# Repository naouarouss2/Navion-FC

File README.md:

# Navion FC

## What is it
It is a small all-in-one flight controller used for autonomous vehicles.

It will run Ardupilot and is compatible with any type of autonomous vehicles.

## Features ✅
-  Barometer
-  IMU
-  Magnometer
-  10 PWM outputs
-  PPM/SBUS input
-  4 Neopixel outputs
-  MicroSD Card Reader
-  USB-C Connector
-  SWD Debugging Interface
-  3 UART Headers
-  1 USART Header
-  1 I²C Header
-  Safety Switch Header
-  16MB External Flash
-  Battery Voltage Monitoring
-  Up to 40V battery input voltage
## Why do I want to make it ? 🛠️

I have always been passionate about autonomous vehicles and wanted to build a universal solution that can run all of the vehicles I'll be building in the future.

That's why I made my flight controller extremely modular and versatile.

## How does it work ?

-  You attach all of your ESCs and Servos to the PWM outputs.

-  Attach neopixel strips to the top neopixel headers (You should power them externally).

-  Connect a standard Pixhawk 2.4.8 (or similar) GPS module (You need to swap the connectors for JST-XH connectors) to the GPS and I²C headers.

-  Connect the battery to the battery header.

-  Connect the RC receiver to the PPM/SBUS header (and configure it accordingly later).

-  Connect a telemetry module to the USART2 header.

-  You can connect other UART accessories like a Lidar to the UART2 and UART3 headers.

-  Then you configure your peripherals in **Mission Planner**, setup your flight controller, plan a mission, and you should be good to go !

## PCB 

### Schematic

### Routing

### 3D View

## 3D Deisgn 🎨

## Firmware

This flight controller will run a custom ported version of the **[Ardupilot firmware](https://github.com/ArduPilot/ardupilot)**

## Disclaimer ⚠️

This project is still untested.

## Credits ❤️
Project made by : **Oussama NAOUAR**

Total logged working hours : **40 hrs**

Made as part of the **Hack Club Fallout** program.

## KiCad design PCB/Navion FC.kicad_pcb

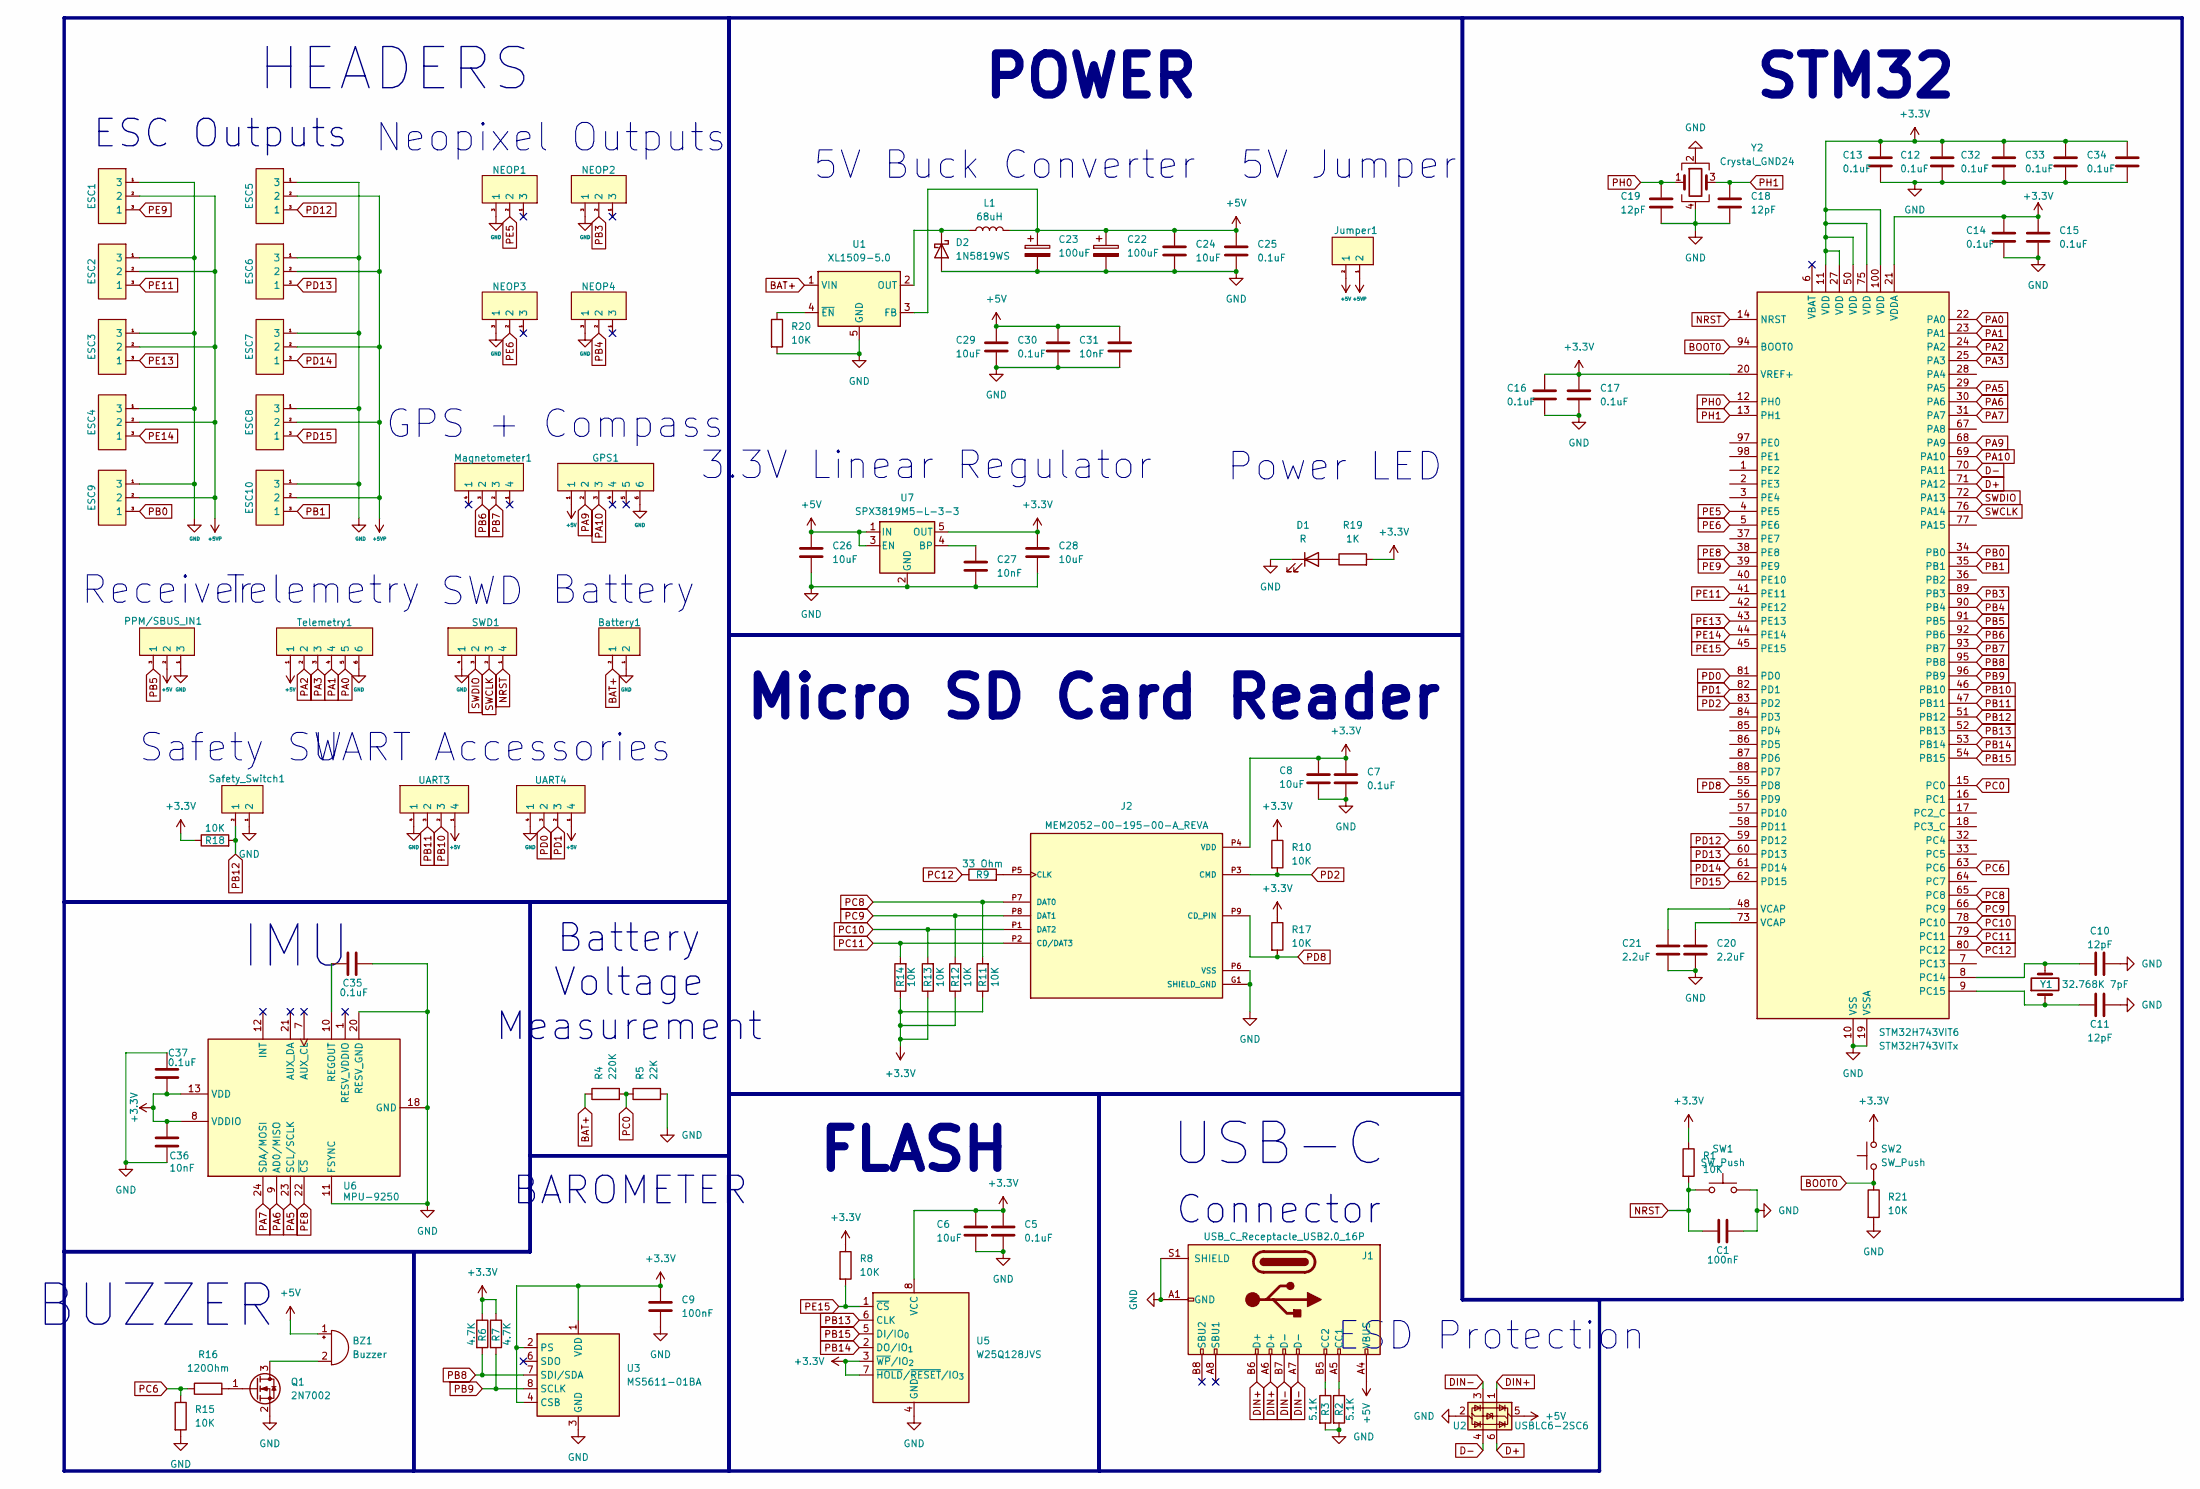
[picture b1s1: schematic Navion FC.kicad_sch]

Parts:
BZ1: Buzzer; Buzzer_12x9.5RM7.6
Battery1: JST_XH_B2B-XH-A_1x02_P2.50mm_Vertical
C1, C9: 100nF; C_0603_1608Metric
C5, C7, C12, C13, C14, C15, C16, C17, C25, C30, C32, C33, C34, C35, C37: 0.1uF; C_0603_1608Metric
C6, C8, C24, C26, C28, C29: 10uF; C_0603_1608Metric
C10, C11, C18, C19: 12pF; C_0603_1608Metric
C20, C21: 2.2uF; C_0603_1608Metric
C22, C23: 100uF; CP_EIA-3528-21_Kemet-B
C27, C31, C36: 10nF; C_0603_1608Metric
D1: R; LED_0603_1608Metric
D2: 1N5819WS; D_SOD-323
ESC1, ESC2, ESC3, ESC4, ESC5, ESC6, ESC7, ESC8, ESC9, ESC10: PinHeader_1x03_P2.54mm_Vertical
GPS1: JST_XH_B6B-XH-A_1x06_P2.50mm_Vertical
J1: USB_C_Receptacle_USB2.0_16P; USB_C_Receptacle_HCTL_HC-TYPE-C-16P-01A
J2: MEM2052-00-195-00-A_REVA; GCT_MEM2052-00-195-00-A_REVA; PARTREV A
Jumper1: PinHeader_1x02_P2.54mm_Vertical
L1: 68uH; L_Sunlord_SWPA8040S
Magnetometer1: JST_XH_B4B-XH-A_1x04_P2.50mm_Vertical
NEOP1, NEOP2, NEOP3, NEOP4: JST_XH_B3B-XH-A_1x03_P2.50mm_Vertical
PPM/SBUS_IN1: PinHeader_1x03_P2.54mm_Vertical
Q1: 2N7002; SOT-23
R1, R8, R10, R11, R12, R13, R14, R15, R17, R18, R20, R21: 10K; R_0603_1608Metric
R2, R3: 5.1K; R_0603_1608Metric
R4: 220K; R_0603_1608Metric
R5: 22K; R_0603_1608Metric
R6, R7: 4.7K; R_0603_1608Metric
R9: 33 Ohm; R_0603_1608Metric
R16: 120Ohm; R_0603_1608Metric
R19: 1K; R_0603_1608Metric
STM32H743VIT6: STM32H743VITx; LQFP-100_14x14mm_P0.5mm
SW1, SW2: SW_Push; SW_PUSH_6mm
SWD1: JST_XH_B4B-XH-A_1x04_P2.50mm_Vertical
Safety_Switch1: JST_XH_B2B-XH-A_1x02_P2.50mm_Vertical
Telemetry1: JST_XH_B6B-XH-A_1x06_P2.50mm_Vertical
U1: XL1509-5.0; SOIC-8_3.9x4.9mm_P1.27mm
U2: USBLC6-2SC6; SOT-23-6
U3: MS5611-01BA; LGA-8_3x5mm_P1.25mm
U5: W25Q128JVS; SOIC-8_5.3x5.3mm_P1.27mm
U6: MPU-9250; InvenSense_QFN-24_3x3mm_P0.4mm
U7: SPX3819M5-L-3-3; SOT-23-5
UART3, UART4: JST_XH_B4B-XH-A_1x04_P2.50mm_Vertical
Y1: 32.768K 7pF; Crystal_SMD_3215-2Pin_3.2x1.5mm
Y2: Crystal_GND24; Crystal_SMD_3225-4Pin_3.2x2.5mm

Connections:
+3.3V: C5.1, C6.1, C7.1, C8.1, C9.1, C12.1, C13.1, C14.1, C15.1, C16.1, C17.1, C28.1, C32.1, C33.1, C34.1, C36.2, C37.1, J2.P4 (VDD), R1.1, R6.1, R7.1, R8.1, R10.1, R11.1, R12.1, R13.1, R14.1, R17.1, R18.1, R19.2, STM32H743VIT6.11 (VDD), STM32H743VIT6.20 (VREF+), STM32H743VIT6.21 (VDDA), STM32H743VIT6.27 (VDD), STM32H743VIT6.50 (VDD), STM32H743VIT6.75 (VDD), STM32H743VIT6.100 (VDD), SW2.2, U3.1 (VDD), U3.2 (PS), U3.4 (CSB), U3.5 (CSB), U5.3 (~WP/IO_{2}), U5.7 (~HOLD/~RESET/IO_{3}), U5.8 (VCC), U6.8 (VDDIO), U6.13 (VDD), U7.5 (OUT)
+5V: BZ1.1 (+), C22.1, C23.1, C24.1, C25.1, C26.1, C29.1, C30.1, C31.1, GPS1.1, J1.A4 (VBUS), J1.A9 (VBUS), J1.B4 (VBUS), J1.B9 (VBUS), Jumper1.2 (1), L1.2, PPM/SBUS_IN1.2, Telemetry1.1, U1.3 (FB), U2.5 (VBUS), U7.1 (IN), U7.3 (EN), UART3.1 (4), UART4.1 (4)
+5VP: ESC1.2, ESC2.2, ESC3.2, ESC4.2, ESC5.2, ESC6.2, ESC7.2, ESC8.2, ESC9.2, ESC10.2, Jumper1.1 (2)
BAT+: Battery1.2 (1), R4.1, U1.1 (VIN)
BOOT0: R21.1, STM32H743VIT6.94 (BOOT0), SW2.1
D+: STM32H743VIT6.71 (PA12), U2.6 (I/O1)
D-: STM32H743VIT6.70 (PA11), U2.4 (I/O2)
DIN+: J1.A6 (D+), J1.B6 (D+), U2.1 (I/O1)
DIN-: J1.A7 (D-), J1.B7 (D-), U2.3 (I/O2)
GND: Battery1.1 (2), C1.2, C5.2, C6.2, C7.2, C8.2, C9.2, C10.2, C11.2, C12.2, C13.2, C14.2, C15.2, C16.2, C17.2, C18.2, C19.2, C20.2, C21.2, C22.2, C23.2, C24.2, C25.2, C26.2, C27.2, C28.2, C29.2, C30.2, C31.2, C32.2, C33.2, C34.2, C35.2, C36.1, C37.2, D1.1 (K), D2.2 (A), ESC1.1 (3), ESC2.1 (3), ESC3.1 (3), ESC4.1 (3), ESC5.1 (3), ESC6.1 (3), ESC7.1 (3), ESC8.1 (3), ESC9.1 (3), ESC10.1 (3), GPS1.6, J1.A1 (GND), J1.A12 (GND), J1.B1 (GND), J1.B12 (GND), J1.S1 (SHIELD), J2.G1 (SHIELD_GND), J2.G2 (SHIELD_GND), J2.G3 (SHIELD_GND), J2.G4 (SHIELD_GND), J2.P6 (VSS), NEOP1.3 (1), NEOP2.3 (1), NEOP3.3 (1), NEOP4.3 (1), PPM/SBUS_IN1.1 (3), Q1.2 (S), R2.2, R3.2, R5.2, R15.2, R20.2, R21.2, STM32H743VIT6.10 (VSS), STM32H743VIT6.19 (VSSA), STM32H743VIT6.26 (VSS), STM32H743VIT6.49 (VSS), STM32H743VIT6.74 (VSS), STM32H743VIT6.99 (VSS), SW1.2, SWD1.4 (1), Safety_Switch1.1 (2), Telemetry1.6, U1.5 (GND), U1.6 (GND), U1.7 (GND), U1.8 (GND), U2.2 (GND), U3.3 (GND), U5.4 (GND), U6.11 (FSYNC), U6.18 (GND), U6.20 (RESV_GND), U7.2 (GND), UART3.4 (1), UART4.4 (1), Y2.2, Y2.4
NRST: C1.1, R1.2, STM32H743VIT6.14 (NRST), SW1.1, SWD1.1 (4)
unnamed: BZ1.2 (-), Q1.3 (D)
unnamed: C20.1, STM32H743VIT6.73 (VCAP)
unnamed: C21.1, STM32H743VIT6.48 (VCAP)
unnamed: D1.2 (A), R19.1
unnamed: D2.1 (K), L1.1, U1.2 (OUT)
unnamed: J1.A5 (CC1), R2.1
unnamed: J1.B5 (CC2), R3.1
unnamed: J2.P5 (CLK), R9.2
unnamed: Q1.1 (G), R16.2
unnamed: C10.1, STM32H743VIT6.8 (PC14), Y1.2
unnamed: C11.1, STM32H743VIT6.9 (PC15), Y1.1
unnamed: R20.1, U1.4 (~EN)
unnamed: C35.1, U6.10 (REGOUT)
unnamed: C27.1, U7.4 (BP)
PA0: STM32H743VIT6.22 (PA0), Telemetry1.5
PA1: STM32H743VIT6.23 (PA1), Telemetry1.4
PA2: STM32H743VIT6.24 (PA2), Telemetry1.2
PA3: STM32H743VIT6.25 (PA3), Telemetry1.3
PA5: STM32H743VIT6.29 (PA5), U6.23 (SCL/SCLK)
PA6: STM32H743VIT6.30 (PA6), U6.9 (AD0/MISO)
PA7: STM32H743VIT6.31 (PA7), U6.24 (SDA/MOSI)
PA9: GPS1.2, STM32H743VIT6.68 (PA9)
PA10: GPS1.3, STM32H743VIT6.69 (PA10)
PB0: ESC9.3 (1), STM32H743VIT6.34 (PB0)
PB1: ESC10.3 (1), STM32H743VIT6.35 (PB1)
PB3: NEOP2.2, STM32H743VIT6.89 (PB3)
PB4: NEOP4.2, STM32H743VIT6.90 (PB4)
PB5: PPM/SBUS_IN1.3 (1), STM32H743VIT6.91 (PB5)
PB6: Magnetometer1.3 (2), STM32H743VIT6.92 (PB6)
PB7: Magnetometer1.2 (3), STM32H743VIT6.93 (PB7)
PB8: R6.2, STM32H743VIT6.95 (PB8), U3.7 (SDI/SDA)
PB9: R7.2, STM32H743VIT6.96 (PB9), U3.8 (SCLK)
PB10: STM32H743VIT6.46 (PB10), UART3.2 (3)
PB11: STM32H743VIT6.47 (PB11), UART3.3 (2)
PB12: R18.2, STM32H743VIT6.51 (PB12), Safety_Switch1.2 (1)
PB13: STM32H743VIT6.52 (PB13), U5.6 (CLK)
PB14: STM32H743VIT6.53 (PB14), U5.2 (DO/IO_{1})
PB15: STM32H743VIT6.54 (PB15), U5.5 (DI/IO_{0})
PC0: R4.2, R5.1, STM32H743VIT6.15 (PC0)
PC6: R15.1, R16.1, STM32H743VIT6.63 (PC6)
PC8: J2.P7 (DAT0), R11.2, STM32H743VIT6.65 (PC8)
PC9: J2.P8 (DAT1), R12.2, STM32H743VIT6.66 (PC9)
PC10: J2.P1 (DAT2), R13.2, STM32H743VIT6.78 (PC10)
PC11: J2.P2 (CD/DAT3), R14.2, STM32H743VIT6.79 (PC11)
PC12: R9.1, STM32H743VIT6.80 (PC12)
PD0: STM32H743VIT6.81 (PD0), UART4.3 (2)
PD1: STM32H743VIT6.82 (PD1), UART4.2 (3)
PD2: J2.P3 (CMD), R10.2, STM32H743VIT6.83 (PD2)
PD8: J2.P9 (CD_PIN), R17.2, STM32H743VIT6.55 (PD8)
PD12: ESC5.3 (1), STM32H743VIT6.59 (PD12)
PD13: ESC6.3 (1), STM32H743VIT6.60 (PD13)
PD14: ESC7.3 (1), STM32H743VIT6.61 (PD14)
PD15: ESC8.3 (1), STM32H743VIT6.62 (PD15)
PE5: NEOP1.2, STM32H743VIT6.4 (PE5)
PE6: NEOP3.2, STM32H743VIT6.5 (PE6)
PE8: STM32H743VIT6.38 (PE8), U6.22 (~CS)
PE9: ESC1.3 (1), STM32H743VIT6.39 (PE9)
PE11: ESC2.3 (1), STM32H743VIT6.41 (PE11)
PE13: ESC3.3 (1), STM32H743VIT6.43 (PE13)
PE14: ESC4.3 (1), STM32H743VIT6.44 (PE14)
PE15: R8.2, STM32H743VIT6.45 (PE15), U5.1 (~CS)
PH0: C19.1, STM32H743VIT6.12 (PH0), Y2.1
PH1: C18.1, STM32H743VIT6.13 (PH1), Y2.3
SWCLK: STM32H743VIT6.76 (PA14), SWD1.2 (3)
SWDIO: STM32H743VIT6.72 (PA13), SWD1.3 (2)

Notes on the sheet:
3.3V Linear Regulator
5V Jumper
UART Accessories
Receiver
Power LED
FLASH
Telemetry
GPS + Compass
BUZZER
STM32
Micro SD Card Reader
ESC Outputs
Neopixel Outputs
5V Buck Converter
Battery
BAROMETER
Safety SW
USB-C
IMU
POWER
HEADERS
Battery Voltage Measurement
Connector
ESD Protection
SWD

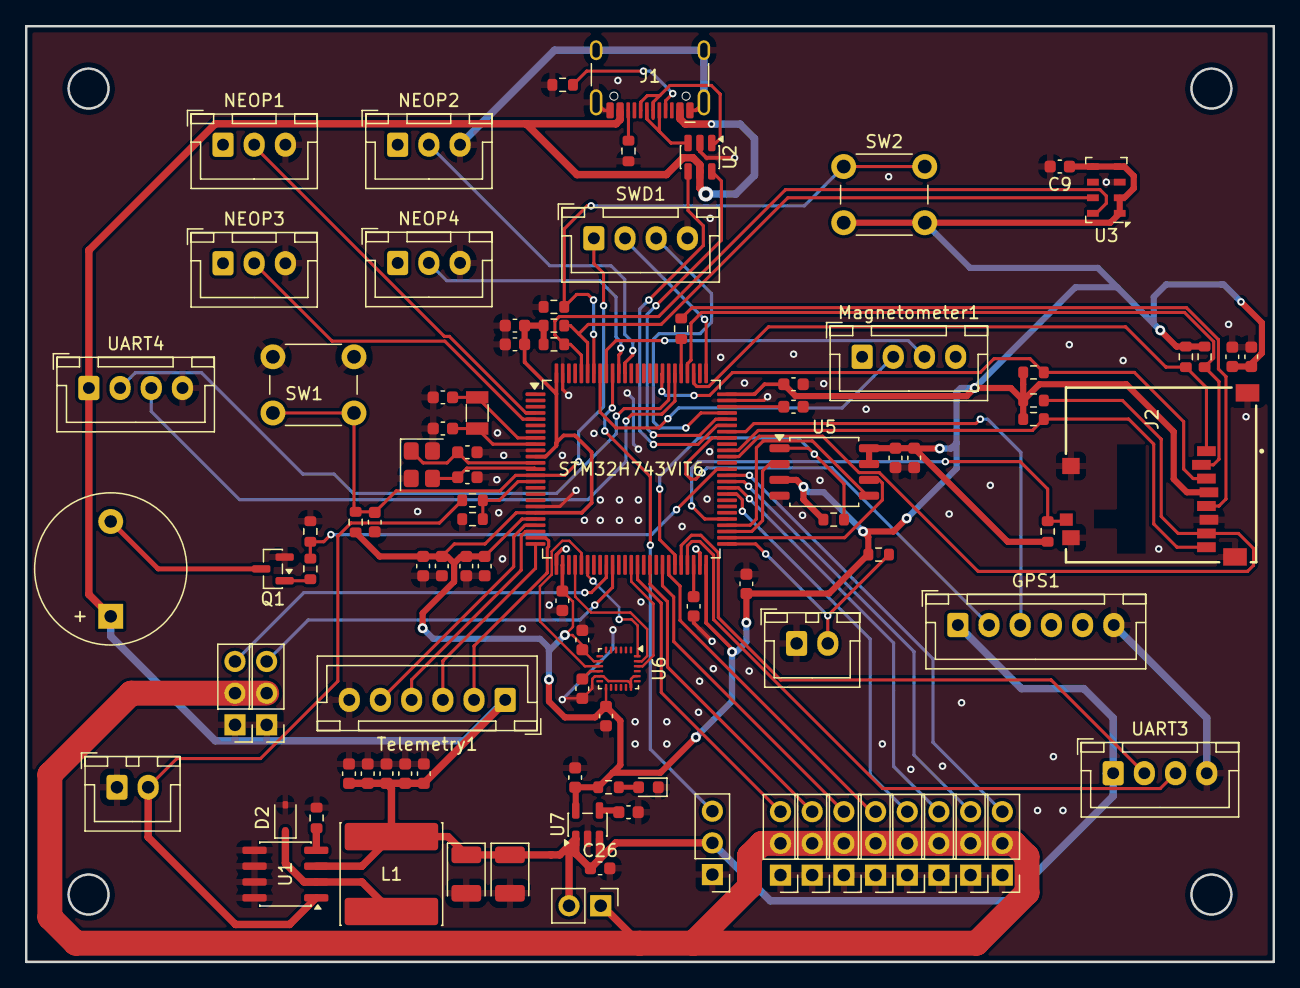
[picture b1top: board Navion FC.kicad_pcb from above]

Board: 4 copper layers, 100.0 x 75.0 mm, 97 parts (0 on the bottom side), 76 nets.

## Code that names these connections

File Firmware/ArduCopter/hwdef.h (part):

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#define PIN_AFIO_AF(n, v)           ((v) << (((n) % 8U) * 4U))

/* PORTA:
 PA11 OTG_FS_DM OTG1 AF10
 PA12 OTG_FS_DP OTG1 AF10
 PA13 JTMS-SWDIO SWD AF0
 PA14 JTCK-SWCLK SWD AF0
*/

#define VAL_GPIOA_MODER   (PIN_MODE_INPUT(0U) | \
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                           PIN_AFIO_AF(15U, 0U))

/* PORTC:
 PC8 SDMMC1_D0 SDMMC1 AF12
 PC9 SDMMC1_D1 SDMMC1 AF12
 PC10 SDMMC1_D2 SDMMC1 AF12
 PC11 SDMMC1_D3 SDMMC1 AF12
 PC12 SDMMC1_CK SDMMC1 AF12
*/

#define VAL_GPIOC_MODER   (PIN_MODE_INPUT(0U) | \
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                           PIN_AFIO_AF(15U, 0U))

/* PORTD:
 PD2 SDMMC1_CMD SDMMC1 AF12
*/

#define VAL_GPIOD_MODER   (PIN_MODE_INPUT(0U) | \
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                           PIN_AFIO_AF(15U, 0U))

/* PORTE:
 PE8 MPU_CS CS
 PE15 FLASH_CS CS
*/

#define VAL_GPIOE_MODER   (PIN_MODE_INPUT(0U) | \
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
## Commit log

2026-06-07 Add README
2026-06-09 Update README with Navion FC details
    Added detailed information about the Navion FC flight controller, including features, purpose, PCB design, and firmware.
2026-06-09 Update README with connection instructions for peripherals
    Added instructions for connecting ESCs, servos, GPS, and other peripherals to the flight controller.
2026-06-09 Fix formatting issues in README.md
2026-06-09 Add disclaimer about project testing status
    Added a disclaimer indicating that the project is untested.
